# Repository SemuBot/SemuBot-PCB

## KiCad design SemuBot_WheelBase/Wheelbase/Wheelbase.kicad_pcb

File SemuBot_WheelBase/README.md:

# Wheelbase

## Components

### BLDC driver

https://www.mouser.ee/ProductDetail/Texas-Instruments/DRV8353FSRTAR?qs=hd1VzrDQEGj9xu7LrY%252BpOw%3D%3D

#### Mosfets

 DI025N06PT-AQ 
 https://www.mouser.ee/ProductDetail/Diotec-Semiconductor/DI025N06PT-AQ?qs=Y0Uzf4wQF3lNF%252Ba3rVyVBQ%3D%3D

#### Oscillator

830205889709
https://www.mouser.ee/ProductDetail/Wurth-Elektronik/830205889709?qs=hWgE7mdIu5QkPZnGbsg1Rg%3D%3D

#### Terminal block connector for 24V from battery

 TB003-500-P02BE

https://www.mouser.ee/ProductDetail/Same-Sky/TB003-500-P02BE?qs=vLWxofP3U2yAT9CFQJ%2FCaw%3D%3D

### USB C connector

https://www.mouser.ee/ProductDetail/Amphenol-FCI/10155435-00011LF?qs=vHuUswq2%252BswoQuNbiiIX%2FQ%3D%3D

### LDO Voltage Regulator
https://www.mouser.ee/ProductDetail/onsemi/NCP164CSN330T1G?qs=xZ%2FP%252Ba9zWqbi%2FAyy5UtoRw%3D%3D

### B5B-XH-A(LF)(SN) HALL Sensor connectors

https://www.mouser.ee/ProductDetail/JST-Commercial/B5B-XH-ALFSN?qs=cdbOS8ANM9ApoXpxtybURg%3D%3D

### ESD Protection

PRTR5V0U2X,215

https://www.mouser.ee/ProductDetail/Nexperia/PRTR5V0U2X215?qs=LOCUfHb8d9sDkgY4cRj8Lw%3D%3D

### Phase connectors for motors

1984620

https://www.snapeda.com/parts/1984620/Phoenix%20Contact/view-part/?ref=search&t=1984620

### Power connector XT30PW-M

https://www.tme.eu/ee/details/xt30pw-m/dc-uhendused/amass/ # 24V
https://www.tme.eu/ee/details/mr30pw-m/dc-uhendused/amass/ # motor

## Pins

* SPI pins for data
* 3x2xGPIO pin for drivers
* 3xPWM for drivers

Hc = Blue
HB = White
Ha = Yellow

Mc = Brown thick
Mb = Green thick
Ma = Orange thick

TOTAL NEEDED FROM STM32: 9(drivers)+ 3CS + SPI =13

### Encoders

* +5V
* DATA
* CLOCK
* GND
* CS

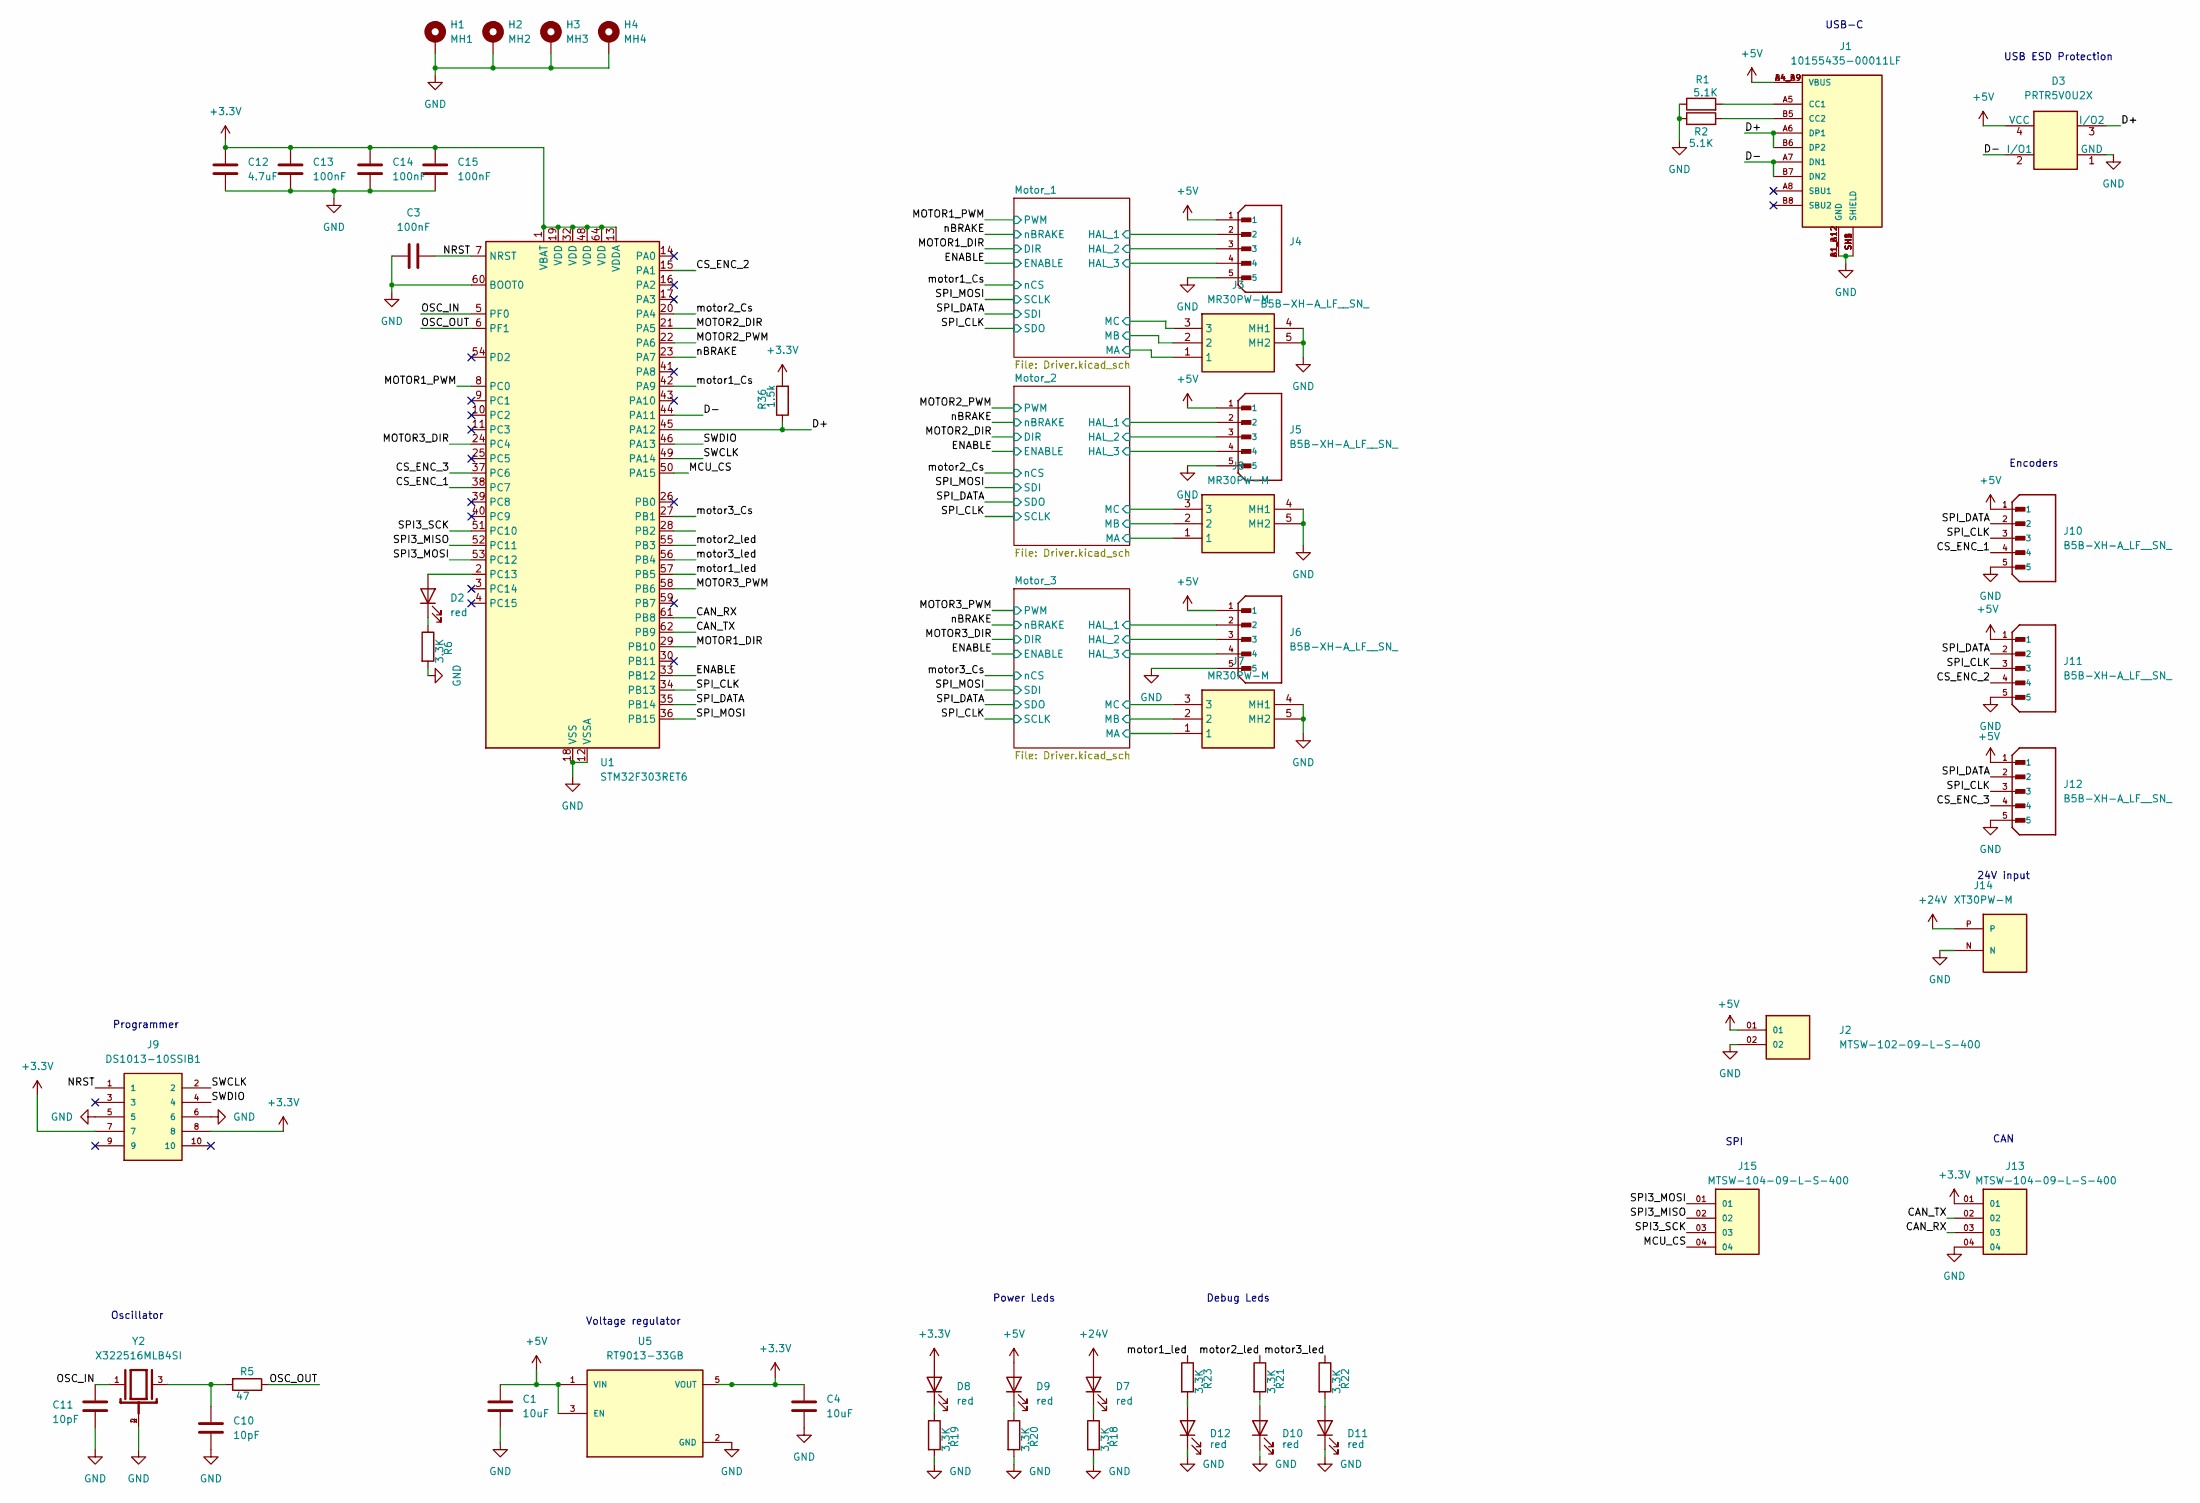
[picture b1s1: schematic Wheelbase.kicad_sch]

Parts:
C1, C4: 10uF; C_0805_2012Metric_Pad1.18x1.45mm_HandSolder
C3, C13, C14, C15: 100nF; C_0603_1608Metric_Pad1.08x0.95mm_HandSolder
C10, C11: 10pF; C_0603_1608Metric_Pad1.08x0.95mm_HandSolder
C12: 4.7uF; C_0603_1608Metric_Pad1.08x0.95mm_HandSolder
D2, D7, D8, D9, D10, D11, D12: red; LED_0603_1608Metric_Pad1.05x0.95mm_HandSolder
D3: PRTR5V0U2X; SOT-143
H1: MH1; MountingHole_3.2mm_M3_Pad_Via
H2: MH2; MountingHole_3.2mm_M3_Pad_Via
H3: MH3; MountingHole_3.2mm_M3_Pad_Via
H4: MH4; MountingHole_3.2mm_M3_Pad_Via
J1: 10155435-00011LF; AMPHENOL_10155435-00011LF; PARTREV C
J2: MTSW-102-09-L-S-400; SAMTEC_MTSW-102-09-L-S-400; PARTREV R
J3, J7, J8: MR30PW-M; MR30PWM; Manufacturer_Part_Number MR30PW-M
J4, J5, J6, J10, J11, J12: B5B-XH-A_LF__SN_; JST_B5B-XH-A_LF__SN_; PARTREV 7/4/21
J9: DS1013-10SSIB1; CONNFLY_DS1013-10SSIB1; PARTREV G
J13, J15: MTSW-104-09-L-S-400; SAMTEC_MTSW-104-09-L-S-400; PARTREV R
J14: XT30PW-M; AMASS_XT30PW-M; PARTREV 1.2
R1, R2: 5.1K; R_0603_1608Metric_Pad0.98x0.95mm_HandSolder
R5: 47; R_0603_1608Metric_Pad0.98x0.95mm_HandSolder
R6, R18, R19, R20, R21, R22, R23: 3.3K; R_0603_1608Metric_Pad0.98x0.95mm_HandSolder
R36: 1.5k; R_0603_1608Metric_Pad0.98x0.95mm_HandSolder
U1: STM32F303RET6; LQFP-64_10x10mm_P0.5mm
U5: RT9013-33GB; SOT94P279X129-5N; PARTREV Aprill 2011
Y2: X322516MLB4SI; OSC_X322516MLB4SI; PARTREV N/A

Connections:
+3.3V: C4.2, C12.1, C13.1, C14.1, C15.1, D8.2 (A), J9.7, J9.8, J13.01, R36.2, U1.1 (VBAT), U1.13 (VDDA), U1.19 (VDD), U1.32 (VDD), U1.48 (VDD), U1.64 (VDD), U5.5 (VOUT)
+5V: C1.2, D3.4 (VCC), D9.2 (A), J1.A4_B9 (VBUS), J1.B4_A9 (VBUS), J2.01, J4.1, J5.1, J6.1, J10.1, J11.1, J12.1, U5.1 (VIN), U5.3 (EN); also elsewhere on the board
+24V: D7.2 (A), J14.P; also elsewhere on the board
/CAN_RX: J13.03, U1.61 (PB8)
/CAN_TX: J13.02, U1.62 (PB9)
/CS_ENC_1: J10.4, U1.38 (PC7)
/CS_ENC_2: J11.4, U1.15 (PA1)
/CS_ENC_3: J12.4, U1.37 (PC6)
/D+: D3.3 (I/O2), J1.A6 (DP1), J1.B6 (DP2), R36.1, U1.45 (PA12)
/D-: D3.2 (I/O1), J1.A7 (DN1), J1.B7 (DN2), U1.44 (PA11)
/ENABLE: U1.33 (PB12); also elsewhere on the board
/MCU_CS: J15.04, U1.50 (PA15)
/MOTOR1_DIR: U1.29 (PB10); also elsewhere on the board
/MOTOR1_PWM: U1.8 (PC0); also elsewhere on the board
/MOTOR2_DIR: U1.21 (PA5); also elsewhere on the board
/MOTOR2_PWM: U1.22 (PA6); also elsewhere on the board
/MOTOR3_DIR: U1.24 (PC4); also elsewhere on the board
/MOTOR3_PWM: U1.58 (PB6); also elsewhere on the board
/Motor_1/HAL_1: J4.2; also elsewhere on the board
/Motor_1/HAL_2: J4.3; also elsewhere on the board
/Motor_1/HAL_3: J4.4; also elsewhere on the board
/Motor_1/SHA: J3.1; also elsewhere on the board
/Motor_1/SHB: J3.2; also elsewhere on the board
/Motor_1/SHC: J3.3; also elsewhere on the board
/Motor_2/HAL_1: J5.2; also elsewhere on the board
/Motor_2/HAL_2: J5.3; also elsewhere on the board
/Motor_2/HAL_3: J5.4; also elsewhere on the board
/Motor_2/SHA: J8.1; also elsewhere on the board
/Motor_2/SHB: J8.2; also elsewhere on the board
/Motor_2/SHC: J8.3; also elsewhere on the board
/Motor_3/HAL_1: J6.2; also elsewhere on the board
/Motor_3/HAL_2: J6.3; also elsewhere on the board
/Motor_3/HAL_3: J6.4; also elsewhere on the board
/Motor_3/SHA: J7.1; also elsewhere on the board
/Motor_3/SHB: J7.2; also elsewhere on the board
/Motor_3/SHC: J7.3; also elsewhere on the board
/NRST: C3.2, J9.1, U1.7 (NRST)
/OSC_IN: C11.1, U1.5 (PF0), Y2.1
/OSC_OUT: R5.1, U1.6 (PF1)
/SPI3_MISO: J15.02, U1.52 (PC11)
/SPI3_MOSI: J15.01, U1.53 (PC12)
/SPI3_SCK: J15.03, U1.51 (PC10)
/SPI_MOSI: U1.36 (PB15); also elsewhere on the board
/SWCLK: J9.2, U1.49 (PA14)
/SWDIO: J9.4, U1.46 (PA13)
/motor1_Cs: U1.42 (PA9); also elsewhere on the board
/motor1_led: R23.1, U1.57 (PB5)
/motor2_Cs: U1.20 (PA4); also elsewhere on the board
/motor2_led: R21.1, U1.55 (PB3)
/motor3_Cs: U1.27 (PB1); also elsewhere on the board
/motor3_led: R22.1, U1.56 (PB4)
/nBRAKE: U1.23 (PA7); also elsewhere on the board
GND: C1.1, C3.1, C4.1, C10.1, C11.2, C12.2, C13.2, C14.2, C15.2, D3.1 (GND), D10.1 (K), D11.1 (K), D12.1 (K), H1.1, H2.1, H3.1, H4.1, J1.A1_B12 (GND), J1.B1_A12 (GND), J1.SH1 (SHIELD), J1.SH2 (SHIELD), J1.SH3 (SHIELD), J1.SH4 (SHIELD), J2.02, J3.4 (MH1), J3.5 (MH2), J4.5, J5.5, J6.5, J7.4 (MH1), J7.5 (MH2), J8.4 (MH1), J8.5 (MH2), J9.5, J9.6, J10.5, J11.5, J12.5, J13.04, J14.N, R1.1, R2.1, R6.2, R18.2, R19.2, R20.2, U1.12 (VSSA), U1.18 (VSS), U1.31 (VSS), U1.47 (VSS), U1.60 (BOOT0), U1.63 (VSS), U5.2 (GND), Y2.2, Y2.4; also elsewhere on the board
unnamed: C10.2, R5.2, Y2.3
unnamed: D2.2 (A), U1.2 (PC13)
unnamed: D2.1 (K), R6.1
unnamed: D7.1 (K), R18.1
unnamed: D8.1 (K), R19.1
unnamed: D9.1 (K), R20.1
unnamed: D10.2 (A), R21.2
unnamed: D11.2 (A), R22.2
unnamed: D12.2 (A), R23.2
unnamed: J1.A5 (CC1), R1.2
unnamed: J1.B5 (CC2), R2.2

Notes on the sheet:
24V input
Encoders
SPI
Debug Leds
Oscillator
USB-C
USB ESD Protection
CAN
Power Leds
Programmer
Voltage regulator

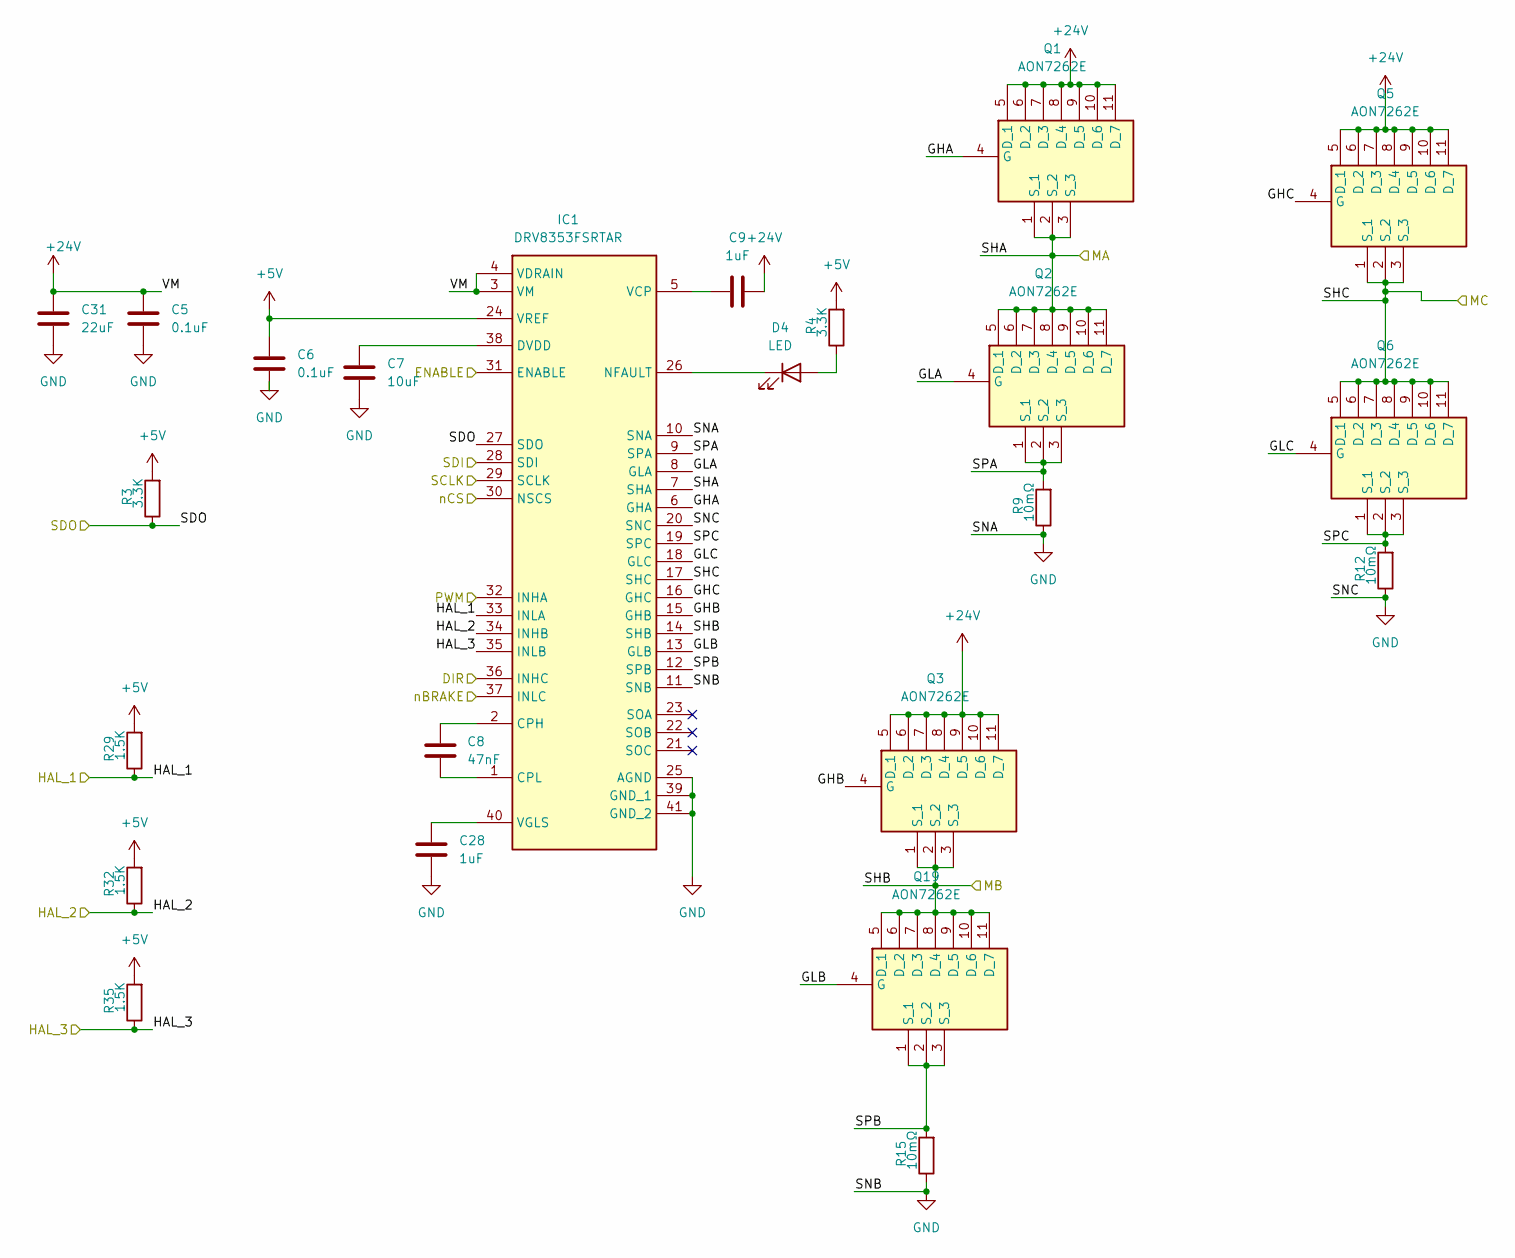
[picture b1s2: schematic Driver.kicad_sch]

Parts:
C5, C6: 0.1uF; C_0603_1608Metric_Pad1.08x0.95mm_HandSolder
C7: 10uF; C_0603_1608Metric_Pad1.08x0.95mm_HandSolder
C8: 47nF; C_0603_1608Metric_Pad1.08x0.95mm_HandSolder
C9, C28: 1uF; C_0603_1608Metric_Pad1.08x0.95mm_HandSolder
C31: 22uF; C_0805_2012Metric_Pad1.18x1.45mm_HandSolder
D4: LED; LED_0603_1608Metric_Pad1.05x0.95mm_HandSolder
IC1: DRV8353FSRTAR; QFN50P600X600X80-41N-D; Mouser Part Number 595-DRV8353FSRTAR
Q1, Q2, Q3, Q5, Q6, Q19: AON7262E; Manufacturer_Part_Number AON7262E
R3, R4: 3.3K; R_0603_1608Metric_Pad0.98x0.95mm_HandSolder
R9, R12, R15: 10mΩ; R_2512_6332Metric_Pad1.40x3.35mm_HandSolder
R29, R32, R35: 1.5K; R_0603_1608Metric_Pad0.98x0.95mm_HandSolder

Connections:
+5V: C6.1, IC1.24 (VREF), R3.2, R4.2, R29.2, R32.2, R35.2; also elsewhere on the board
+24V: C5.1, C9.2, C31.2, IC1.3 (VM), IC1.4 (VDRAIN), Q1.5 (D_1), Q1.6 (D_2), Q1.7 (D_3), Q1.8 (D_4), Q1.9 (D_5), Q1.10 (D_6), Q1.11 (D_7), Q3.5 (D_1), Q3.6 (D_2), Q3.7 (D_3), Q3.8 (D_4), Q3.9 (D_5), Q3.10 (D_6), Q3.11 (D_7), Q5.5 (D_1), Q5.6 (D_2), Q5.7 (D_3), Q5.8 (D_4), Q5.9 (D_5), Q5.10 (D_6), Q5.11 (D_7); also elsewhere on the board
/ENABLE: IC1.31 (ENABLE); also elsewhere on the board
/MOTOR1_DIR: IC1.36 (INHC); also elsewhere on the board
/MOTOR1_PWM: IC1.32 (INHA); also elsewhere on the board
/Motor_1/GHA: IC1.6 (GHA), Q1.4 (G)
/Motor_1/GHB: IC1.15 (GHB), Q3.4 (G)
/Motor_1/GHC: IC1.16 (GHC), Q5.4 (G)
/Motor_1/GLA: IC1.8 (GLA), Q2.4 (G)
/Motor_1/GLB: IC1.13 (GLB), Q19.4 (G)
/Motor_1/GLC: IC1.18 (GLC), Q6.4 (G)
/Motor_1/HAL_1: IC1.33 (INLA), R29.1; also elsewhere on the board
/Motor_1/HAL_2: IC1.34 (INHB), R32.1; also elsewhere on the board
/Motor_1/HAL_3: IC1.35 (INLB), R35.1; also elsewhere on the board
/Motor_1/SHA: IC1.7 (SHA), Q1.1 (S_1), Q1.2 (S_2), Q1.3 (S_3), Q2.5 (D_1), Q2.6 (D_2), Q2.7 (D_3), Q2.8 (D_4), Q2.9 (D_5), Q2.10 (D_6), Q2.11 (D_7); also elsewhere on the board
/Motor_1/SHB: IC1.14 (SHB), Q3.1 (S_1), Q3.2 (S_2), Q3.3 (S_3), Q19.5 (D_1), Q19.6 (D_2), Q19.7 (D_3), Q19.8 (D_4), Q19.9 (D_5), Q19.10 (D_6), Q19.11 (D_7); also elsewhere on the board
/Motor_1/SHC: IC1.17 (SHC), Q5.1 (S_1), Q5.2 (S_2), Q5.3 (S_3), Q6.5 (D_1), Q6.6 (D_2), Q6.7 (D_3), Q6.8 (D_4), Q6.9 (D_5), Q6.10 (D_6), Q6.11 (D_7); also elsewhere on the board
/Motor_1/SPA: IC1.9 (SPA), Q2.1 (S_1), Q2.2 (S_2), Q2.3 (S_3), R9.2
/Motor_1/SPB: IC1.12 (SPB), Q19.1 (S_1), Q19.2 (S_2), Q19.3 (S_3), R15.2
/Motor_1/SPC: IC1.19 (SPC), Q6.1 (S_1), Q6.2 (S_2), Q6.3 (S_3), R12.2
/SPI_MOSI: IC1.29 (SCLK); also elsewhere on the board
/motor1_Cs: IC1.30 (NSCS); also elsewhere on the board
/nBRAKE: IC1.37 (INLC); also elsewhere on the board
GND: C5.2, C6.2, C7.2, C28.1, C31.1, IC1.10 (SNA), IC1.11 (SNB), IC1.20 (SNC), IC1.25 (AGND), IC1.39 (GND_1), IC1.41 (GND_2), R9.1, R12.1, R15.1; also elsewhere on the board
unnamed: D4.2 (A), R4.1
unnamed: D4.1 (K), IC1.26 (NFAULT)
unnamed: C8.1, IC1.2 (CPH)
unnamed: C8.2, IC1.1 (CPL)
unnamed: C7.1, IC1.38 (DVDD)
unnamed: C9.1, IC1.5 (VCP)
unnamed: C28.2, IC1.40 (VGLS)

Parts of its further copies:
C17, C18, C23, C24: 0.1uF; C_0603_1608Metric_Pad1.08x0.95mm_HandSolder
C19, C25: 10uF; C_0603_1608Metric_Pad1.08x0.95mm_HandSolder
C20, C26: 47nF; C_0603_1608Metric_Pad1.08x0.95mm_HandSolder
C21, C27, C29, C30: 1uF; C_0603_1608Metric_Pad1.08x0.95mm_HandSolder
C32, C33: 22uF; C_0805_2012Metric_Pad1.18x1.45mm_HandSolder
D5, D6: LED; LED_0603_1608Metric_Pad1.05x0.95mm_HandSolder
IC2, IC3: DRV8353FSRTAR; QFN50P600X600X80-41N-D; Mouser Part Number 595-DRV8353FSRTAR
Q4, Q7, Q8, Q9, Q10, Q11, Q12, Q13, Q14, Q15, Q20, Q21: AON7262E; Manufacturer_Part_Number AON7262E
R7, R8, R24, R25: 3.3K; R_0603_1608Metric_Pad0.98x0.95mm_HandSolder
R10, R11, R13, R14, R16, R17: 10mΩ; R_2512_6332Metric_Pad1.40x3.35mm_HandSolder
R30, R31, R33, R34, R37, R38: 1.5K; R_0603_1608Metric_Pad0.98x0.95mm_HandSolder

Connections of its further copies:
+5V: C18.1, C24.1, IC2.24 (VREF), IC3.24 (VREF), R7.2, R8.2, R24.2, R25.2, R30.2, R31.2, R33.2, R34.2, R37.2, R38.2; also elsewhere on the board
+24V: C17.1, C21.2, C23.1, C27.2, C32.2, C33.2, IC2.3 (VM), IC2.4 (VDRAIN), IC3.3 (VM), IC3.4 (VDRAIN), Q4.5 (D_1), Q4.6 (D_2), Q4.7 (D_3), Q4.8 (D_4), Q4.9 (D_5), Q4.10 (D_6), Q4.11 (D_7), Q7.5 (D_1), Q7.6 (D_2), Q7.7 (D_3), Q7.8 (D_4), Q7.9 (D_5), Q7.10 (D_6), Q7.11 (D_7), Q9.5 (D_1), Q9.6 (D_2), Q9.7 (D_3), Q9.8 (D_4), Q9.9 (D_5), Q9.10 (D_6), Q9.11 (D_7), Q11.5 (D_1), Q11.6 (D_2), Q11.7 (D_3), Q11.8 (D_4), Q11.9 (D_5), Q11.10 (D_6), Q11.11 (D_7), Q13.5 (D_1), Q13.6 (D_2), Q13.7 (D_3), Q13.8 (D_4), Q13.9 (D_5), Q13.10 (D_6), Q13.11 (D_7), Q15.5 (D_1), Q15.6 (D_2), Q15.7 (D_3), Q15.8 (D_4), Q15.9 (D_5), Q15.10 (D_6), Q15.11 (D_7); also elsewhere on the board
/ENABLE: IC2.31 (ENABLE), IC3.31 (ENABLE); also elsewhere on the board
/MOTOR2_DIR: IC2.36 (INHC); also elsewhere on the board
/MOTOR2_PWM: IC2.32 (INHA); also elsewhere on the board
/MOTOR3_DIR: IC3.36 (INHC); also elsewhere on the board
/MOTOR3_PWM: IC3.32 (INHA); also elsewhere on the board
/Motor_2/GHA: IC2.6 (GHA), Q7.4 (G)
/Motor_2/GHB: IC2.15 (GHB), Q4.4 (G)
/Motor_2/GHC: IC2.16 (GHC), Q11.4 (G)
/Motor_2/GLA: IC2.8 (GLA), Q8.4 (G)
/Motor_2/GLB: IC2.13 (GLB), Q20.4 (G)
/Motor_2/GLC: IC2.18 (GLC), Q10.4 (G)
/Motor_2/HAL_1: IC2.33 (INLA), R30.1; also elsewhere on the board
/Motor_2/HAL_2: IC2.34 (INHB), R33.1; also elsewhere on the board
/Motor_2/HAL_3: IC2.35 (INLB), R37.1; also elsewhere on the board
/Motor_2/SHA: IC2.7 (SHA), Q7.1 (S_1), Q7.2 (S_2), Q7.3 (S_3), Q8.5 (D_1), Q8.6 (D_2), Q8.7 (D_3), Q8.8 (D_4), Q8.9 (D_5), Q8.10 (D_6), Q8.11 (D_7); also elsewhere on the board
/Motor_2/SHB: IC2.14 (SHB), Q4.1 (S_1), Q4.2 (S_2), Q4.3 (S_3), Q20.5 (D_1), Q20.6 (D_2), Q20.7 (D_3), Q20.8 (D_4), Q20.9 (D_5), Q20.10 (D_6), Q20.11 (D_7); also elsewhere on the board
/Motor_2/SHC: IC2.17 (SHC), Q10.5 (D_1), Q10.6 (D_2), Q10.7 (D_3), Q10.8 (D_4), Q10.9 (D_5), Q10.10 (D_6), Q10.11 (D_7), Q11.1 (S_1), Q11.2 (S_2), Q11.3 (S_3); also elsewhere on the board
/Motor_2/SPA: IC2.9 (SPA), Q8.1 (S_1), Q8.2 (S_2), Q8.3 (S_3), R10.2
/Motor_2/SPB: IC2.12 (SPB), Q20.1 (S_1), Q20.2 (S_2), Q20.3 (S_3), R16.2
/Motor_2/SPC: IC2.19 (SPC), Q10.1 (S_1), Q10.2 (S_2), Q10.3 (S_3), R13.2
/Motor_3/GHA: IC3.6 (GHA), Q13.4 (G)
/Motor_3/GHB: IC3.15 (GHB), Q9.4 (G)
/Motor_3/GHC: IC3.16 (GHC), Q15.4 (G)
/Motor_3/GLA: IC3.8 (GLA), Q14.4 (G)
/Motor_3/GLB: IC3.13 (GLB), Q21.4 (G)
/Motor_3/GLC: IC3.18 (GLC), Q12.4 (G)
/Motor_3/HAL_1: IC3.33 (INLA), R31.1; also elsewhere on the board
/Motor_3/HAL_2: IC3.34 (INHB), R34.1; also elsewhere on the board
/Motor_3/HAL_3: IC3.35 (INLB), R38.1; also elsewhere on the board
/Motor_3/SHA: IC3.7 (SHA), Q13.1 (S_1), Q13.2 (S_2), Q13.3 (S_3), Q14.5 (D_1), Q14.6 (D_2), Q14.7 (D_3), Q14.8 (D_4), Q14.9 (D_5), Q14.10 (D_6), Q14.11 (D_7); also elsewhere on the board
/Motor_3/SHB: IC3.14 (SHB), Q9.1 (S_1), Q9.2 (S_2), Q9.3 (S_3), Q21.5 (D_1), Q21.6 (D_2), Q21.7 (D_3), Q21.8 (D_4), Q21.9 (D_5), Q21.10 (D_6), Q21.11 (D_7); also elsewhere on the board
/Motor_3/SHC: IC3.17 (SHC), Q12.5 (D_1), Q12.6 (D_2), Q12.7 (D_3), Q12.8 (D_4), Q12.9 (D_5), Q12.10 (D_6), Q12.11 (D_7), Q15.1 (S_1), Q15.2 (S_2), Q15.3 (S_3); also elsewhere on the board
/Motor_3/SPA: IC3.9 (SPA), Q14.1 (S_1), Q14.2 (S_2), Q14.3 (S_3), R11.2
/Motor_3/SPB: IC3.12 (SPB), Q21.1 (S_1), Q21.2 (S_2), Q21.3 (S_3), R17.2
/Motor_3/SPC: IC3.19 (SPC), Q12.1 (S_1), Q12.2 (S_2), Q12.3 (S_3), R14.2
/SPI_MOSI: IC2.28 (SDI), IC3.28 (SDI); also elsewhere on the board
/motor2_Cs: IC2.30 (NSCS); also elsewhere on the board
/motor3_Cs: IC3.30 (NSCS); also elsewhere on the board
/nBRAKE: IC2.37 (INLC), IC3.37 (INLC); also elsewhere on the board
GND: C17.2, C18.2, C19.2, C23.2, C24.2, C25.2, C29.1, C30.1, C32.1, C33.1, IC2.10 (SNA), IC2.11 (SNB), IC2.20 (SNC), IC2.25 (AGND), IC2.39 (GND_1), IC2.41 (GND_2), IC3.10 (SNA), IC3.11 (SNB), IC3.20 (SNC), IC3.25 (AGND), IC3.39 (GND_1), IC3.41 (GND_2), R10.1, R11.1, R13.1, R14.1, R16.1, R17.1; also elsewhere on the board
unnamed: D5.2 (A), R7.1
unnamed: D5.1 (K), IC2.26 (NFAULT)
unnamed: D6.2 (A), R8.1
unnamed: D6.1 (K), IC3.26 (NFAULT)
unnamed: C20.1, IC2.2 (CPH)
unnamed: C20.2, IC2.1 (CPL)
unnamed: C19.1, IC2.38 (DVDD)
unnamed: C21.1, IC2.5 (VCP)
unnamed: C29.2, IC2.40 (VGLS)
unnamed: C26.1, IC3.2 (CPH)
unnamed: C26.2, IC3.1 (CPL)
unnamed: C25.1, IC3.38 (DVDD)
unnamed: C27.1, IC3.5 (VCP)
unnamed: C30.2, IC3.40 (VGLS)

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
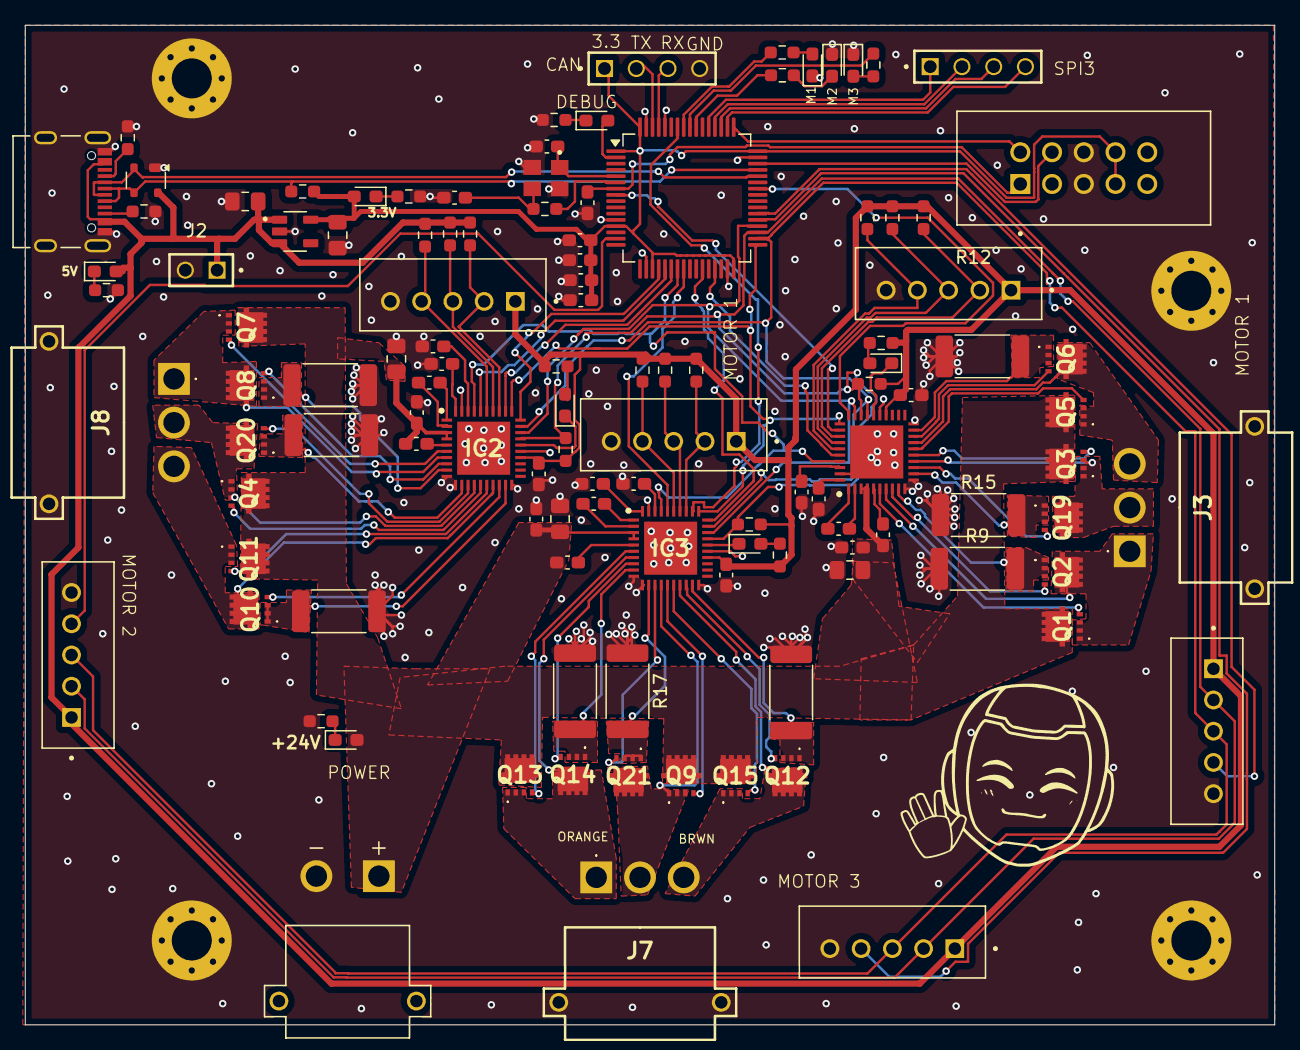
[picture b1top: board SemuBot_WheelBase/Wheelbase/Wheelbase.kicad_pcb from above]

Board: 2 copper layers, 100.0 x 80.0 mm, 119 parts (0 on the bottom side), 114 nets.

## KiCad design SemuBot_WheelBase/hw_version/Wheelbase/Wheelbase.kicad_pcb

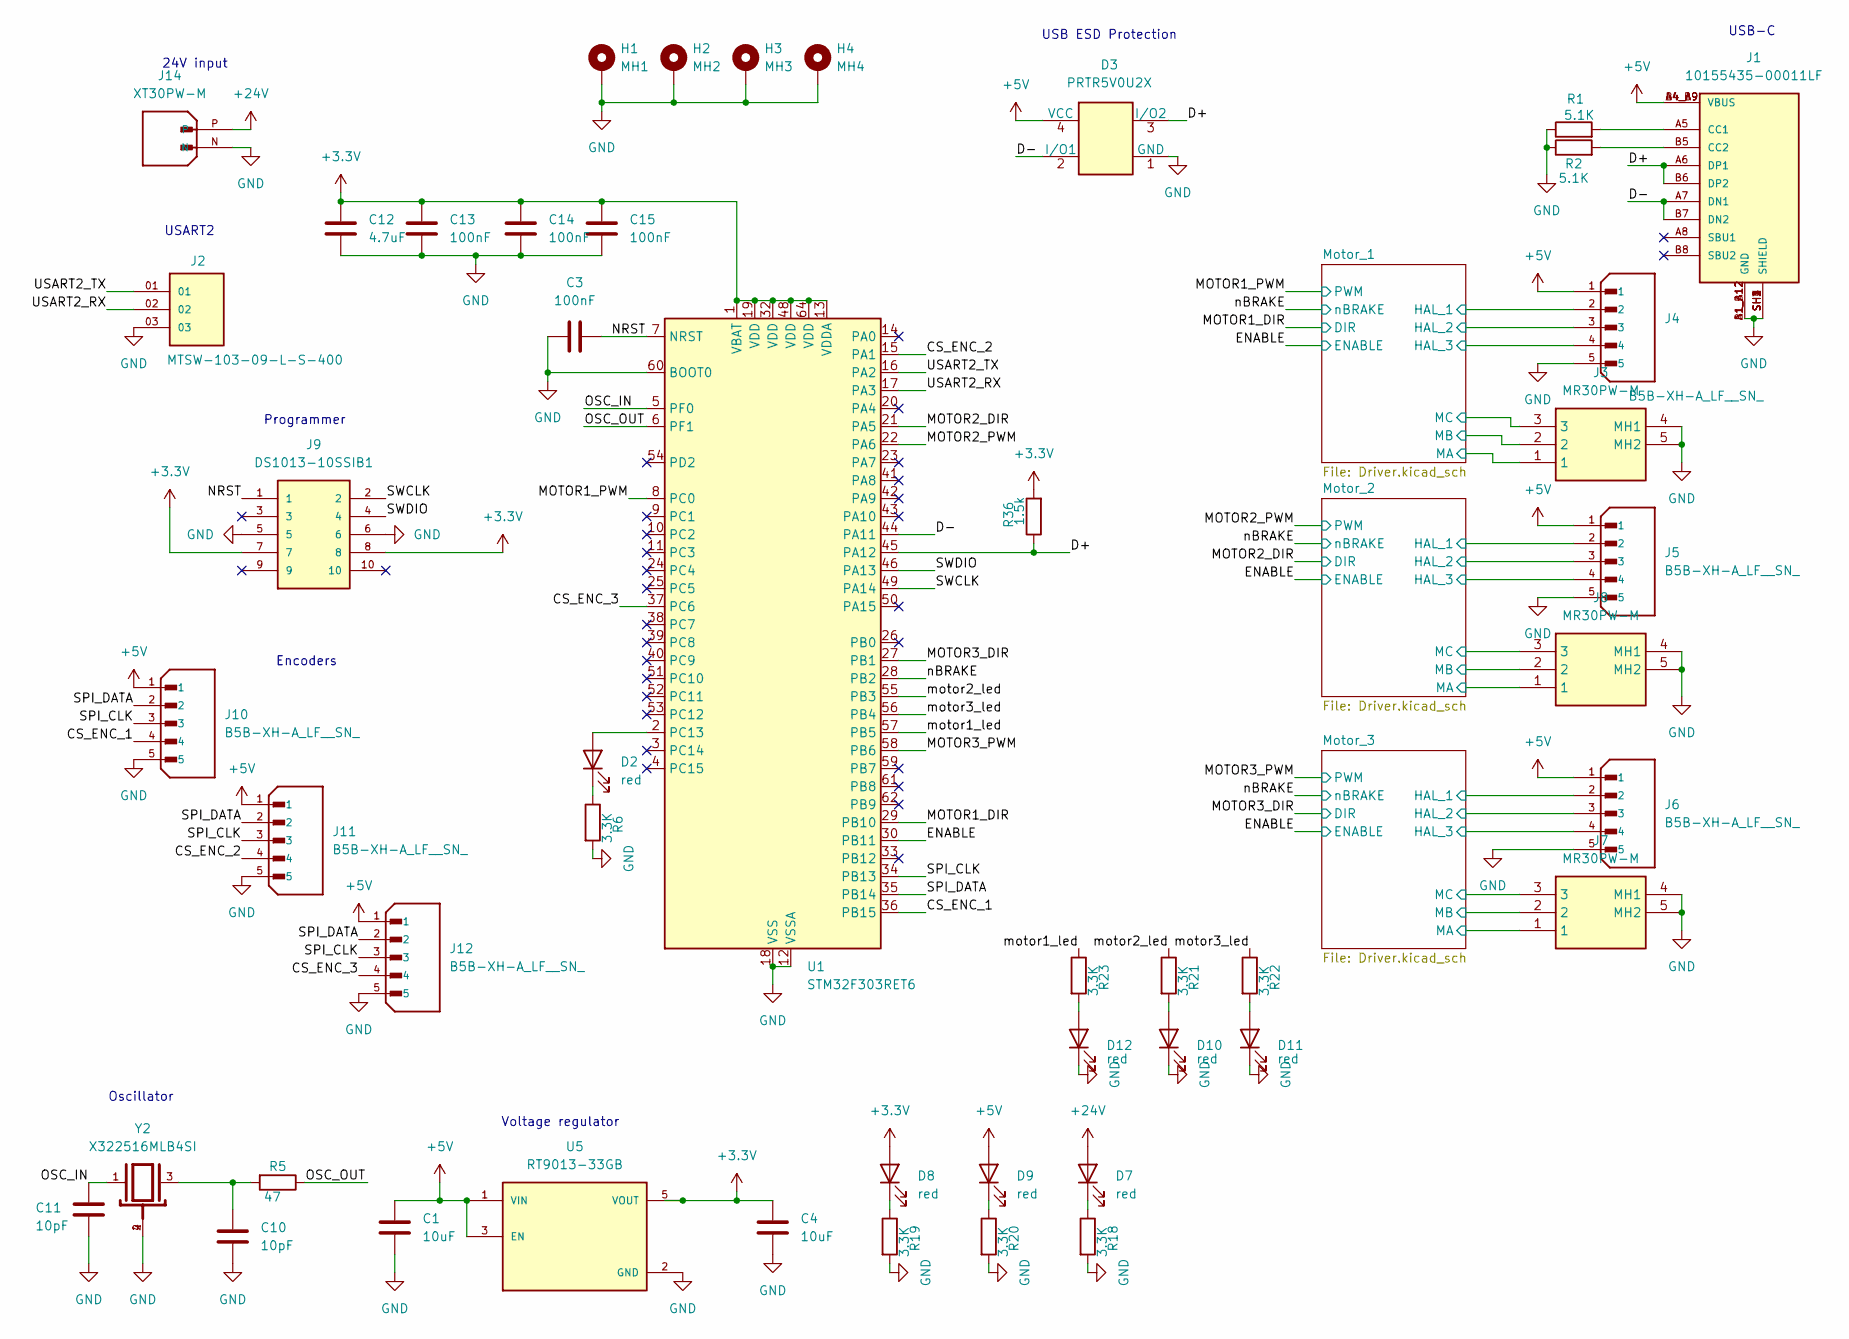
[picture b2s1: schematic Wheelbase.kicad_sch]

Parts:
C1, C4: 10uF; C_0805_2012Metric_Pad1.18x1.45mm_HandSolder
C3, C13, C14, C15: 100nF; C_0603_1608Metric_Pad1.08x0.95mm_HandSolder
C10, C11: 10pF; C_0603_1608Metric_Pad1.08x0.95mm_HandSolder
C12: 4.7uF; C_0603_1608Metric_Pad1.08x0.95mm_HandSolder
D2, D7, D8, D9, D10, D11, D12: red; LED_0603_1608Metric_Pad1.05x0.95mm_HandSolder
D3: PRTR5V0U2X; SOT-143
H1: MH1; MountingHole_2.2mm_M2_Pad_Via
H2: MH2; MountingHole_2.2mm_M2_Pad_Via
H3: MH3; MountingHole_2.2mm_M2_Pad_Via
H4: MH4; MountingHole_2.2mm_M2_Pad_Via
J1: 10155435-00011LF; AMPHENOL_10155435-00011LF; PARTREV C
J2: MTSW-103-09-L-S-400; SAMTEC_MTSW-103-09-L-S-400; PARTREV R
J3, J7, J8: MR30PW-M; MR30PWM; Manufacturer_Part_Number MR30PW-M
J4, J5, J6, J10, J11, J12: B5B-XH-A_LF__SN_; JST_B5B-XH-A_LF__SN_; PARTREV 7/4/21
J9: DS1013-10SSIB1; CONNFLY_DS1013-10SSIB1; PARTREV G
J14: XT30PW-M; AMASS_XT30PW-M; PARTREV 1.2
R1, R2: 5.1K; R_0603_1608Metric_Pad0.98x0.95mm_HandSolder
R5: 47; R_0603_1608Metric_Pad0.98x0.95mm_HandSolder
R6, R18, R19, R20, R21, R22, R23: 3.3K; R_0603_1608Metric_Pad0.98x0.95mm_HandSolder
R36: 1.5k; R_0603_1608Metric_Pad0.98x0.95mm_HandSolder
U1: STM32F303RET6; LQFP-64_10x10mm_P0.5mm
U5: RT9013-33GB; SOT94P279X129-5N; PARTREV Aprill 2011
Y2: X322516MLB4SI; OSC_X322516MLB4SI; PARTREV N/A

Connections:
+3.3V: C4.2, C12.1, C13.1, C14.1, C15.1, D8.2 (A), J9.7, J9.8, R36.2, U1.1 (VBAT), U1.13 (VDDA), U1.19 (VDD), U1.32 (VDD), U1.48 (VDD), U1.64 (VDD), U5.5 (VOUT)
+5V: C1.2, D3.4 (VCC), D9.2 (A), J1.A4_B9 (VBUS), J1.B4_A9 (VBUS), J4.1, J5.1, J6.1, J10.1, J11.1, J12.1, U5.1 (VIN), U5.3 (EN); also elsewhere on the board
+24V: D7.2 (A), J14.P; also elsewhere on the board
/CS_ENC_1: J10.4, U1.36 (PB15)
/CS_ENC_2: J11.4, U1.15 (PA1)
/CS_ENC_3: J12.4, U1.37 (PC6)
/D+: D3.3 (I/O2), J1.A6 (DP1), J1.B6 (DP2), R36.1, U1.45 (PA12)
/D-: D3.2 (I/O1), J1.A7 (DN1), J1.B7 (DN2), U1.44 (PA11)
/ENABLE: U1.30 (PB11); also elsewhere on the board
/MOTOR1_DIR: U1.29 (PB10); also elsewhere on the board
/MOTOR1_PWM: U1.8 (PC0); also elsewhere on the board
/MOTOR2_DIR: U1.21 (PA5); also elsewhere on the board
/MOTOR2_PWM: U1.22 (PA6); also elsewhere on the board
/MOTOR3_DIR: U1.27 (PB1); also elsewhere on the board
/MOTOR3_PWM: U1.58 (PB6); also elsewhere on the board
/Motor_1/HAL_1: J4.2; also elsewhere on the board
/Motor_1/HAL_2: J4.3; also elsewhere on the board
/Motor_1/HAL_3: J4.4; also elsewhere on the board
/Motor_1/SHA: J3.1; also elsewhere on the board
/Motor_1/SHB: J3.2; also elsewhere on the board
/Motor_1/SHC: J3.3; also elsewhere on the board
/Motor_2/HAL_1: J5.2; also elsewhere on the board
/Motor_2/HAL_2: J5.3; also elsewhere on the board
/Motor_2/HAL_3: J5.4; also elsewhere on the board
/Motor_2/SHA: J8.1; also elsewhere on the board
/Motor_2/SHB: J8.2; also elsewhere on the board
/Motor_2/SHC: J8.3; also elsewhere on the board
/Motor_3/HAL_1: J6.2; also elsewhere on the board
/Motor_3/HAL_2: J6.3; also elsewhere on the board
/Motor_3/HAL_3: J6.4; also elsewhere on the board
/Motor_3/SHA: J7.1; also elsewhere on the board
/Motor_3/SHB: J7.2; also elsewhere on the board
/Motor_3/SHC: J7.3; also elsewhere on the board
/NRST: C3.2, J9.1, U1.7 (NRST)
/OSC_IN: C11.1, U1.5 (PF0), Y2.1
/OSC_OUT: R5.1, U1.6 (PF1)
/SPI_CLK: J10.3, J11.3, J12.3, U1.34 (PB13)
/SPI_DATA: J10.2, J11.2, J12.2, U1.35 (PB14)
/SWCLK: J9.2, U1.49 (PA14)
/SWDIO: J9.4, U1.46 (PA13)
/USART2_RX: J2.02, U1.17 (PA3)
/USART2_TX: J2.01, U1.16 (PA2)
/motor1_led: R23.1, U1.57 (PB5)
/motor2_led: R21.1, U1.55 (PB3)
/motor3_led: R22.1, U1.56 (PB4)
/nBRAKE: U1.28 (PB2); also elsewhere on the board
GND: C1.1, C3.1, C4.1, C10.1, C11.2, C12.2, C13.2, C14.2, C15.2, D3.1 (GND), D10.1 (K), D11.1 (K), D12.1 (K), H1.1, H2.1, H3.1, H4.1, J1.A1_B12 (GND), J1.B1_A12 (GND), J1.SH1 (SHIELD), J1.SH2 (SHIELD), J1.SH3 (SHIELD), J1.SH4 (SHIELD), J2.03, J3.4 (MH1), J3.5 (MH2), J4.5, J5.5, J6.5, J7.4 (MH1), J7.5 (MH2), J8.4 (MH1), J8.5 (MH2), J9.5, J9.6, J10.5, J11.5, J12.5, J14.N, R1.1, R2.1, R6.2, R18.2, R19.2, R20.2, U1.12 (VSSA), U1.18 (VSS), U1.31 (VSS), U1.47 (VSS), U1.60 (BOOT0), U1.63 (VSS), U5.2 (GND), Y2.2, Y2.4; also elsewhere on the board
unnamed: C10.2, R5.2, Y2.3
unnamed: D2.2 (A), U1.2 (PC13)
unnamed: D2.1 (K), R6.1
unnamed: D7.1 (K), R18.1
unnamed: D8.1 (K), R19.1
unnamed: D9.1 (K), R20.1
unnamed: D10.2 (A), R21.2
unnamed: D11.2 (A), R22.2
unnamed: D12.2 (A), R23.2
unnamed: J1.A5 (CC1), R1.2
unnamed: J1.B5 (CC2), R2.2

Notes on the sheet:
24V input
Encoders
Oscillator
USB-C
USB ESD Protection
USART2
Programmer
Voltage regulator
